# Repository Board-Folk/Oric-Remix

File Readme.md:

# Oric Remix

An updated Oric-1 / Oric Atmos board

This repository contains the Bill-of-Materials (BOM), Gerbers and Kicad files for an updated Tangerine Oric motherboard found in the Oric-1 and Oric Atmos computers. The board is compatible for system ROM, in software and in form factor with the original board. Improvements include integration of service manual modifications, updated RAM and ROM layout and composite video, with the added intention to make it easier to build. It does not replace any of the core chips including the ULA which is still required.

There was an issue with v1.1 board causing the /ROMDIS signal not disabling the internal ROM. Simon Luce discovered this in testing and devised a fix that is now incorporated into v1.2.  Many thanks to Simon. This has now been tested with the Loci expansion which now starts correctly. A suggested method of applying this fix is further down the page.

## Revisions

* Version 1.1 Initial Public Release
* Version 1.2 fix for external expansions (/ROMDIS fix)

Project now in Kicad 9

### Version 1.1 Modifications from Original

* LM7805 voltage regulator
* 27C512 ROM with 4 bank selector
* Additional AY-3-8910 socket
* Integrated tape mods (inc service manual)
* Replacement /ROMDIS logic
* AD724 composite & stereo sound output
* Speaker volume control
* 4464 RAM
* Additional system reset button
* Commodore 1531 tape interface (optional - original remains on the board)

### Version 1.2

* /ROMDIS fix

## Modification Notes

### LM7805

The original Oric boards regulated the negative power rail using a 7905 voltage regulator, keeping the positive rail common across the board and to the power supply. This has been replaced with a 7805 regulator making the ground common instead. This makes it easier to replace the regulator with something more modern and common. It has to be noted though this may cause issues sharing a power adapter with other expansions that also regulate on the negative rail, depending on how they connect to the system through the interface port. If this is the case separate power adapters should be used. We'll be testing this in time, and we're pretty sure this will have caused terrible problems for the original board too as the original regulator doesn't make a whole lot of sense for driving logic.

### ROM replacement and /ROMDIS updated

For the use of EPROMs and the bank selector, /ROMDIS was updated, the logic which allows external expansions to disable the system ROM. This uses IC11 which can no longer be omitted. This logic has been fixed in v1.2.

A 27C512 EEPROM can be used in chunks of 16KB selectable with the DIP switch. To compile a ROM of this kind, simply concatenate 4 16KB ROM images together, for example in DOS, copy /b rom1.bin+rom2.bin+rom3.bin+rom4.bin bigrom.bin to give you a 64KB file and select each 16KB banks with the switches as binary.

### AY-3-8910 socket

The AY-3-8910 can be fitted instead of the AY-3-8912 sound chip. There's no difference in function and good ones can be found more cheaply.

### Integrated Tape Mods

There were two tape mods, one from the the service manual and one from an assembled original, which have been included on the board. From the service manual page 71, modification 8, R11 and C19 "Improved Cassette Loading". R101 and C101 were also found on an original assembled board. This second mod should not be fitted for boards assembled with the 1531 tape interface.

### AD724 Composite Output

The original PROM based composite generation for the RF modulator wasn't good at all. This has been replaced with an AD724 and a 3.5mm TRRS output jack which also includes Stereo audio out, in the same channel configuration as you'd have on an Amstrad CPC464/6128. Sleeve is ground you'll need an OMTP wired cable connection.

### Speaker Volume Control

The original Oric was too loud. This adjusts the volume. Within the footprint of the volume control, there's a header for connection of an external potentiometer instead.

### System Reset Button

An additional push button has been added, with alternative pin header LK6 for external connection. This is a separate CPU reset, the original pulls down /NMI.

### Commodore 1531 Tape Port

To cut a long story short, tape support isn't great on the Oric, a source tape has to be near perfect, or you need a Maxduino. There was space on the board after all the other mods, and the schematics fitted well. It doesn't need to be fitted which is why the BOM is listed separately. The original tape connection and relay are still there with the original 7 pin DIN on the back. You can fit both fine, so long as R101 and C101 aren't fitted. It's just a cool feature and nice to have, though might upset some purists.

## Keyboard

We'll try get a keyboard replica done as soon as we can, modified for the use of MX or compatible keyswitches. There's at least one other replica already available on the internet.

A prototype PS/2 interface has been completed and works which isn't any use with an original case, but at least makes a functional system. The board also has provision for USB, the code for which hasn't been completed yet. This prototype will be uploaded soon. Still trying to work out how this will work out for a final version and whether that can fit inside a case.

## BOM

### Main BOM

Main BOM including items for Commodore 1531 Cassette. See below. Resistors 1/4W. Ceramic caps 5.08mm. Electrolytics and Tants all radial.

|Qty|Reference(s)|Value|Type|Notes|
|:--:|:--:|:--:|:--:|:--:|
|1|R1|10R|Resistor||
|1|R2|4K7|Resistor||
|10|R4,R7,R9-R11,R13,R40-R42,R56|1K|Resistor||
|1|R101|1K|Resistor|Do not fit for C1531|
|6|R5,R43-R45,R47,R49|10K|Resistor||
|1|R6|220K|Resistor||
|1|R8|100K|Resistor||
|3|R12,R46,R48|22K|Resistor||
|2|R24,R25|47K|Resistor||
|1|R26|2K2|Resistor||
|1|R30|220R|Resistor||
|3|R37-R39|270R|Resistor||
|1|R31|560R|Resistor||
|4|R32,R34-R36|75R|Resistor||
|1|C8|100uF 16V|Electrolytic||
|1|C4|2.2uF 16V|Electrolytic||
|1|C21|10uF 16V|Electrolytic||
|1|C1|22uF 16V|Electrolytic||
|1|C24|220uF 16V|Electrolytic||
|2|C3,C36|100uF Tant|Tantalum||
|1|C33|10pF|Ceramic||
|1|C26|120pF|Ceramic||
|1|C19|2.2nF|Ceramic||
|1|C101|2.2nF|Ceramic|Do not fit for C1531|
|1|C5|10nF|Ceramic||
|1|C9|220nF|Ceramic||
|5|C25,C28,C30-C32|100nF|Ceramic||
|14|C2,C7,C10-C17,C22-C23,C34,C35|47nF|Ceramic||
|1|VC1|5-20pF Trimmer|Trimmer|CVN6500|
|1|D1|1N4148|Small Signal Diode||
|1|D32|3mm LED|LED||
|1|IC1|LM7805|Voltage Regulator||
|1|IC2|LM386|IC||
|1|IC3|LM358|IC||
|1|IC4|AY-3-8912|IC|IC4 or IC10|
|1|IC10|AY-3-8910|IC|Not both|
|1|IC5|6502A|IC||
|1|IC6|6522A|IC||
|1|IC7|HCS10017|IC||
|2|IC8,IC20|74LS257|IC||
|1|IC9|27C128-27C512 ROM|IC||
|1|IC11|74LS00|IC|Clock and /ROMDIS (now a requirement)|
|1|IC21|74LS04|IC||
|1|IC22|74LS365|IC||
|1|IC23|AD724JR|IC||
|1|IC30,IC31|4464 RAM|IC||
|3|TR1-TR3|BC549|Transistor||
|1|RP1|2K2 SIP8 Bussed|Resistor Network||
|1|RP2|220R SIP8 Isolated|Resistor Network||
|1|RP3|10K SIP8 Isolated|Resistor Network||
|1|RV2|5K/10K 3386 Potentiometer|Potentiometer|5K recommended|
|1|SW1|Reset Switch (NMI)|Push Switch|Original or 6mm Push Switch|
|1|SW2|2 position DIP4 Switch|DIP Switch|Optional ROM Bank Selector 0-3 128Kb/512Kb|
|1|SW3|Reset Switch (System)|Push Switch|6mm Push Switch|
|1|RL1|Oki D51A05P|Relay||
|1|LS1|Philips AD2071/Z25|Speaker||
|1|XT1|12MHz|Crystal|HC-49/U recommended|
|1|XT2|4.43MHz|Crystal|HC-49/U recommended|
|1|SK1|5 pin DIN Socket|Socket||
|1|SK2|7 pin DIN Socket|Socket|Short, board pins 2 row, needs recommendation|
|1|SK3|2.1mm DC Barrel Jack|Socket||
|1|SK4|3.5mm TRRS Jack|Socket|PJ320A for OMTP connection|
|1|PL1|2x10 right angle pin header|Header||
|1|PL2|2x17 right angle header|Header||
|1|PL3|14 pin header|Header||

### Commodore 1531 Port BOM

|Qty|Reference(s)|Value|Type|Notes|
|:--:|:--:|:--:|:--:|:--:|
|2|R50,R51|220R|Resistor||
|1|R53|1K|Resistor||
|2|R54,R55|1K5|Resistor||
|1|C37|100nF|Ceramic||
|1|D30|1N4737A|Zener Diode|7.5V|
|1|D31|3mm LED|LED|Motor LED|
|2|TR4,TR5|BC547|Transistor||
|1|TR6|BC337|Transistor||
|1|TR7|TIP29|Transistor|D880 Substitute|
|1|SK5|7 pin mini-DIN|Socket||

## Version v1.1 /ROMDIS Fix

Version 1.1 of the board can be reasonably easily modified to incorporate the fix. Here's a suggested method.

* Cut the track to south side of IC11 pin 1 on the rear of the board
* Cut the track between pins 4 and 5 of IC11 on the rear of the board. If these pins are soldered you may wish to remove the solder first and reapply.
* Scrape to remove the solder mask on the thin track north of pin 5 on the rear of the board carefully not to expose the thicker 5V track above and re-tin.
* Solder a thin bridge wire between the exposed track and pin 5 of IC11

See image at the bottom of the page.

## Links

   [Finedon Electronics - Short 7 pin DIN socket](https://www.ebay.co.uk/itm/185588182650) <br>
   [Mike Brown's Diagnostic ROM](https://oric.signal11.org.uk/html/diagrom.htm)

## Credits

Original replica PCB Layout by Rob Taylor (@peepouk) with modifications by Ian Cudlip (@grandoldian). Original PCB, research, assistance and documentation from Chrissy (@chris_jh). Schematics recreated and modifications by Ian Cudlip with suggestions and testing from Chrissy. /ROMDIS fix by Simon Luce.

## Thanks

* "More Fun Making It" Lee (@morefunmakingit) 
* Marko Šolajić (@msolajic)
* Simon Luce
* The Board Folk Team

## Gallery

Oric Remix v1.1 in Black<br>

<br>
Version v1.1 /ROMDIS Fix<br>

## Legal

As the product of this project is a replica of a proprietary product, the the author makes no claim of copyright to the schematics nor PCB layouts and releases these into the public domain, solely for the purposes of study and historical preservation.

You are free to produce PCBs based on this project's designs at your own risk and without limitation, for your own use or for sale and/or repair at a reasonable price. Attribution is appreciated. The authors are not obliged to provide support of any kind. 

Under no circumstances will the authors be held responsible or liable in any way for losses, damages or costs resulting from the use of the information and/or resources of this project. 

The resources are provided "as-is" without warranty of any kind, either expressed or implied, including, but not limited to, the implied warranties of merchantability and fitness for a particular purpose.

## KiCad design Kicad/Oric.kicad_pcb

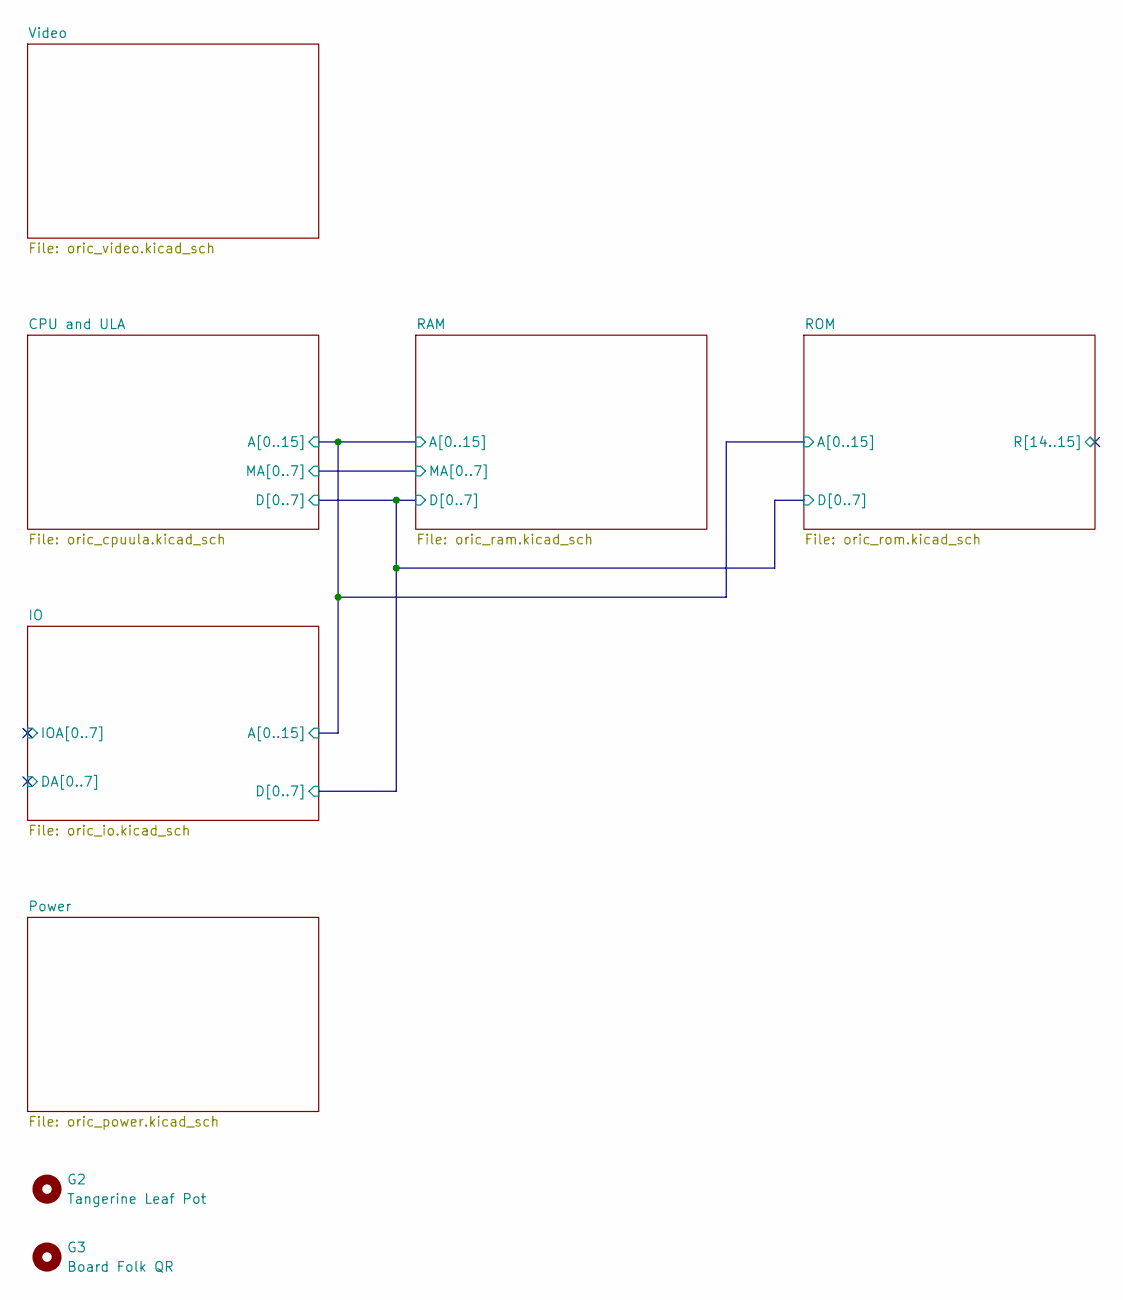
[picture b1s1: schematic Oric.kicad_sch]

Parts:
G2: Tangerine Leaf Pot; tangerineleafpot_growth1
G3: Board Folk QR; bf_qr14

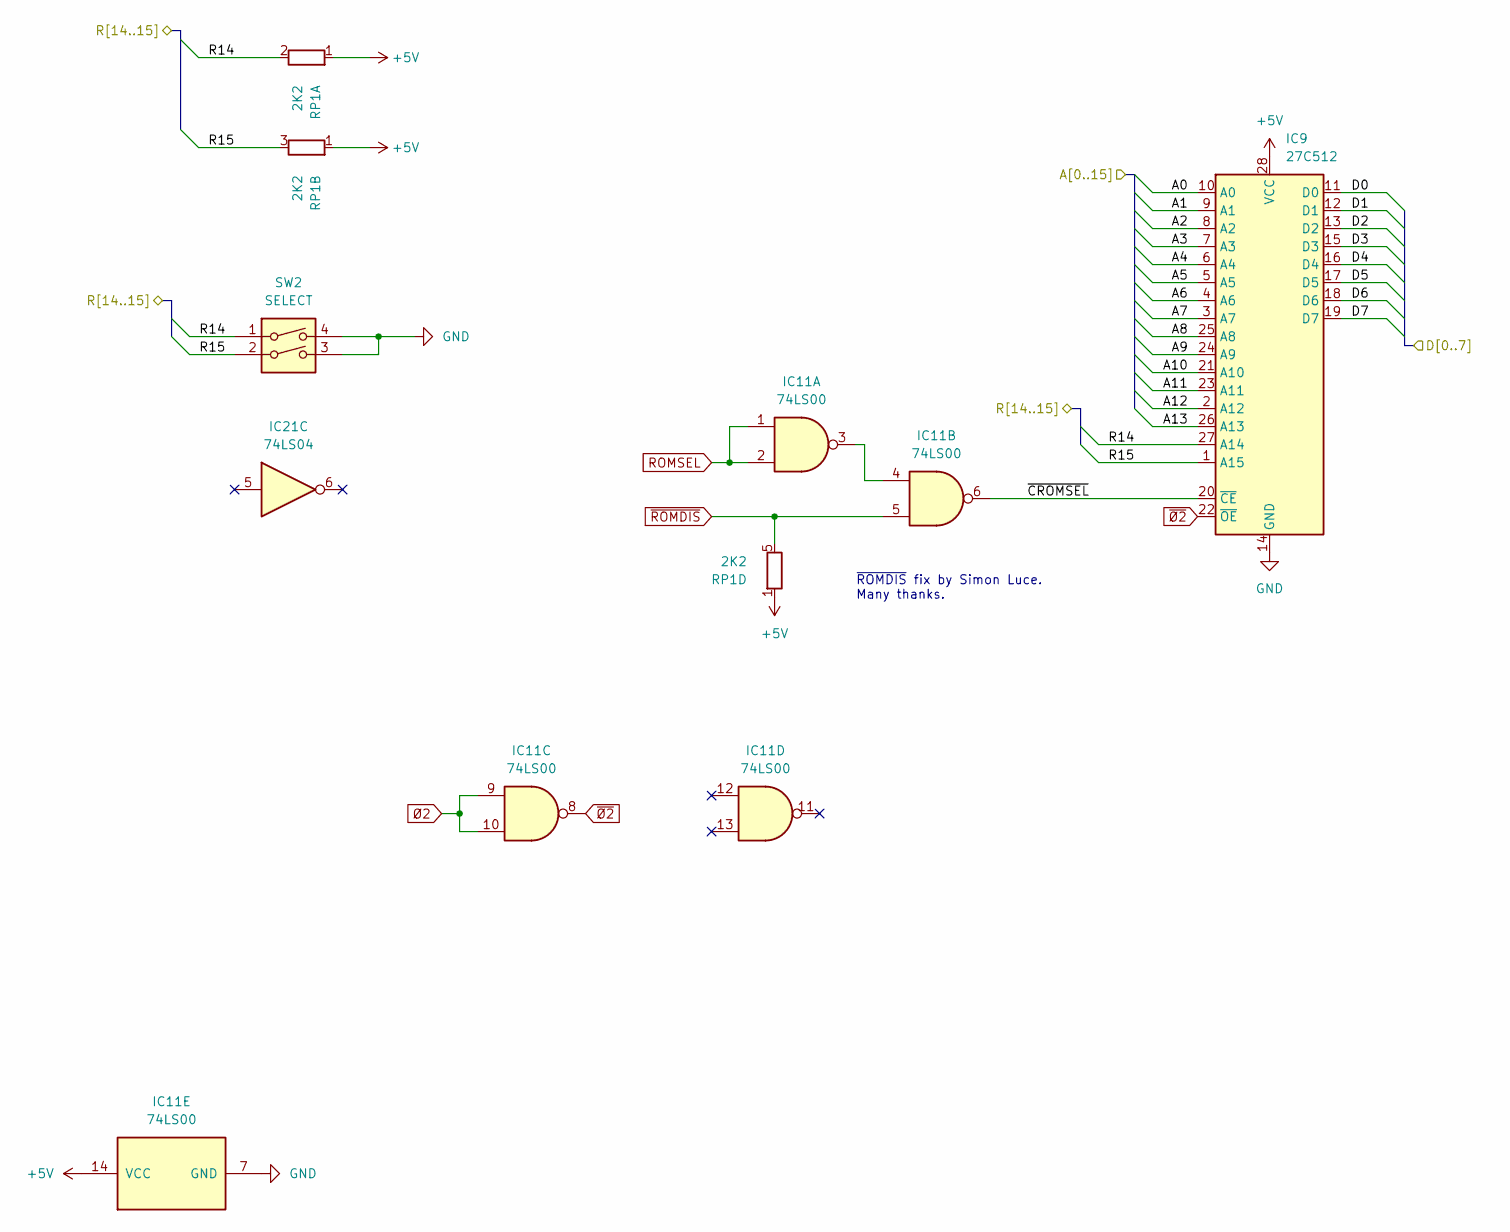
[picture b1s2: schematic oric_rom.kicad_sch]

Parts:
IC9: 27C512; DIP-28_W15.24mm
IC11: 74LS00; DIP-14_W7.62mm
IC21: 74LS04; DIP-14_W7.62mm
RP1: 2K2; R_Array_SIP8_Bussed
SW2: SELECT; ROM_Switch

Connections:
+5V: IC9.28 (VCC), IC11.14 (VCC), RP1.1 (R1); also elsewhere on the board
/CPU and ULA/A0: IC9.10 (A0); also elsewhere on the board
/CPU and ULA/A1: IC9.9 (A1); also elsewhere on the board
/CPU and ULA/A2: IC9.8 (A2); also elsewhere on the board
/CPU and ULA/A3: IC9.7 (A3); also elsewhere on the board
/CPU and ULA/A4: IC9.6 (A4); also elsewhere on the board
/CPU and ULA/A5: IC9.5 (A5); also elsewhere on the board
/CPU and ULA/A6: IC9.4 (A6); also elsewhere on the board
/CPU and ULA/A7: IC9.3 (A7); also elsewhere on the board
/CPU and ULA/A8: IC9.25 (A8); also elsewhere on the board
/CPU and ULA/A9: IC9.24 (A9); also elsewhere on the board
/CPU and ULA/A10: IC9.21 (A10); also elsewhere on the board
/CPU and ULA/A11: IC9.23 (A11); also elsewhere on the board
/CPU and ULA/A12: IC9.2 (A12); also elsewhere on the board
/CPU and ULA/A13: IC9.26 (A13); also elsewhere on the board
/CPU and ULA/D0: IC9.11 (D0); also elsewhere on the board
/CPU and ULA/D1: IC9.12 (D1); also elsewhere on the board
/CPU and ULA/D2: IC9.13 (D2); also elsewhere on the board
/CPU and ULA/D3: IC9.15 (D3); also elsewhere on the board
/CPU and ULA/D4: IC9.16 (D4); also elsewhere on the board
/CPU and ULA/D5: IC9.17 (D5); also elsewhere on the board
/CPU and ULA/D6: IC9.18 (D6); also elsewhere on the board
/CPU and ULA/D7: IC9.19 (D7); also elsewhere on the board
/ROM/R14: IC9.27 (A14), RP1.2 (R1.2), SW2.1
/ROM/R15: IC9.1 (A15), RP1.3 (R2.2), SW2.2
/ROM/~CROMSEL: IC9.20 (~CE), IC11.6
GND: IC9.14 (GND), IC11.7 (GND), SW2.3, SW2.4; also elsewhere on the board
unnamed: IC11.3, IC11.4
ROMSEL: IC11.1, IC11.2; also elsewhere on the board
~ROMDIS: IC11.5, RP1.5 (R4.2); also elsewhere on the board
~Ø2: IC9.22 (~OE), IC11.8
Ø2: IC11.9, IC11.10; also elsewhere on the board

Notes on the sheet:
~{ROMDIS} fix by Simon Luce. Many thanks.

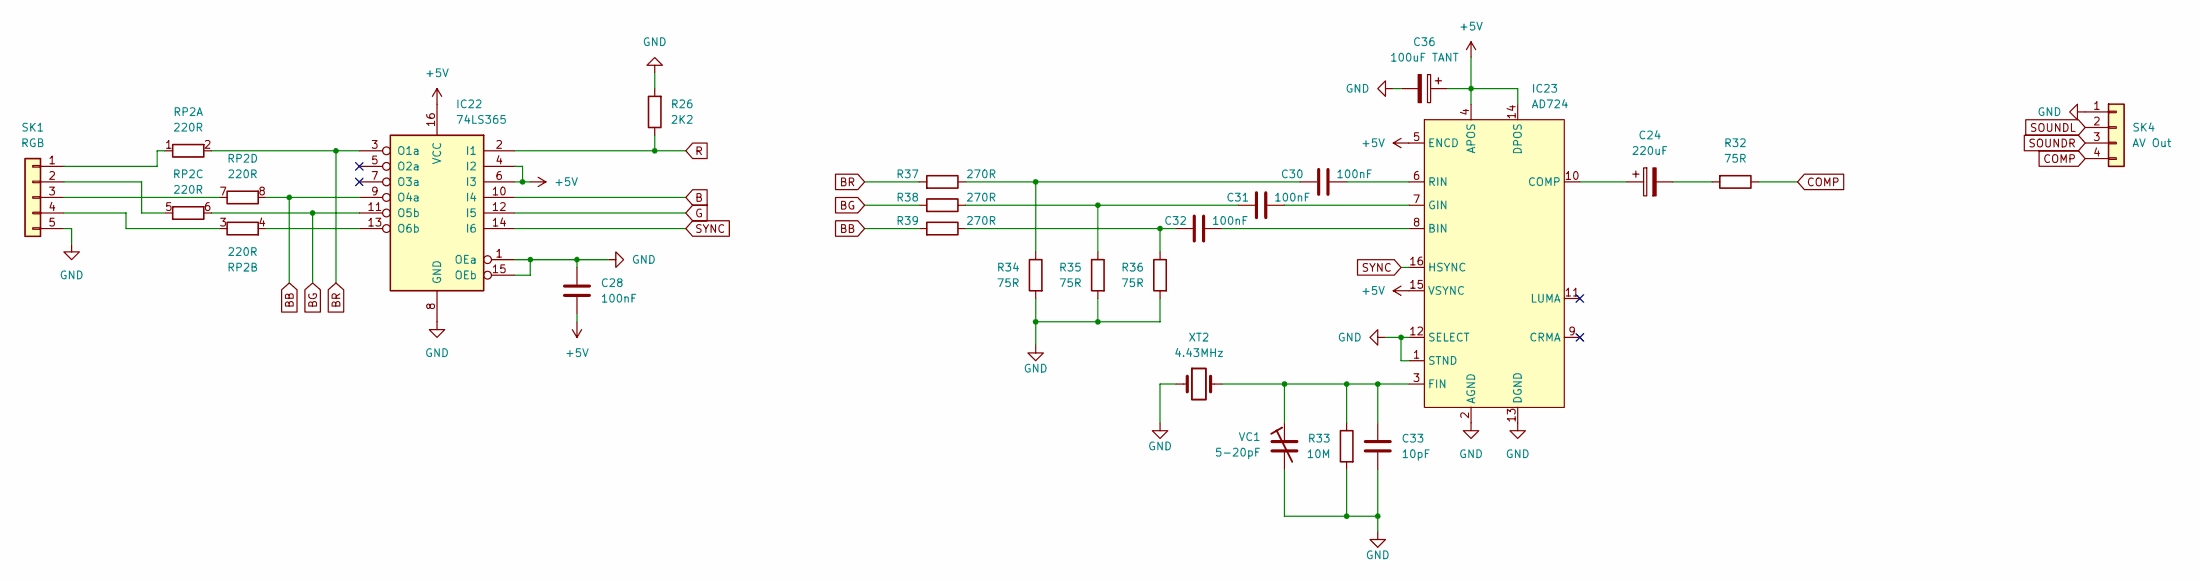
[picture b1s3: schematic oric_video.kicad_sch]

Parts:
C24: 220uF; Electrolytic Capacitor 5.00mm
C28, C30, C31, C32: 100nF; Ceramic Capacitor 5.00mm
C33: 10pF; Ceramic Capacitor 5.00mm
C36: 100uF TANT; Tantalum Capacitor 5.00mm
IC22: 74LS365; DIP-16_W7.62mm
IC23: AD724; SOIC-16W_7.5x10.3mm_P1.27mm
R26: 2K2; Resistor 10.16mm
R32, R34, R35, R36: 75R; Resistor 10.16mm
R33: 10M; Resistor 10.16mm
R37, R38, R39: 270R; Resistor 10.16mm
RP2: 220R; R_Array_SIP8_Isolated
SK1: RGB; SK1_5-Pin_DIN
SK4: AV Out; PJ320A
VC1: 5-20pF; CVN6500
XT2: 4.43MHz; Crystal

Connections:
+5V: C28.2, C36.1, IC22.4 (I2), IC22.6 (I3), IC22.16 (VCC), IC23.4 (APOS), IC23.5 (ENCD), IC23.14 (DPOS), IC23.15 (VSYNC); also elsewhere on the board
B: IC22.10 (I4); also elsewhere on the board
BB: IC22.9 (O4a), R39.2, RP2.8 (R4.2)
BG: IC22.11 (O5b), R38.2, RP2.6 (R3.2)
BR: IC22.3 (O1a), R37.2, RP2.2 (R1.2)
COMP: R32.1, SK4.4
G: IC22.12 (I5); also elsewhere on the board
GND: C28.1, C33.1, C36.2, IC22.1 (OEa), IC22.8 (GND), IC22.15 (OEb), IC23.1 (STND), IC23.2 (AGND), IC23.12 (SELECT), IC23.13 (DGND), R26.2, R33.2, R34.2, R35.2, R36.2, SK1.5, SK4.1, VC1.2, XT2.1; also elsewhere on the board
unnamed: C24.2, R32.2
unnamed: C30.1, R34.1, R37.1
unnamed: C31.1, R35.1, R38.1
unnamed: C32.1, R36.1, R39.1
unnamed: IC22.13 (O6b), RP2.4 (R2.2)
unnamed: C32.2, IC23.8 (BIN)
unnamed: C24.1, IC23.10 (COMP)
unnamed: C33.2, IC23.3 (FIN), R33.1, VC1.1, XT2.2
unnamed: C31.2, IC23.7 (GIN)
unnamed: C30.2, IC23.6 (RIN)
unnamed: RP2.1 (R1.1), SK1.1
unnamed: RP2.3 (R2.1), SK1.4
unnamed: RP2.5 (R3.1), SK1.2
unnamed: RP2.7 (R4.1), SK1.3
R: IC22.2 (I1), R26.1; also elsewhere on the board
SOUNDL: SK4.2; also elsewhere on the board
SOUNDR: SK4.3; also elsewhere on the board
SYNC: IC22.14 (I6), IC23.16 (HSYNC); also elsewhere on the board

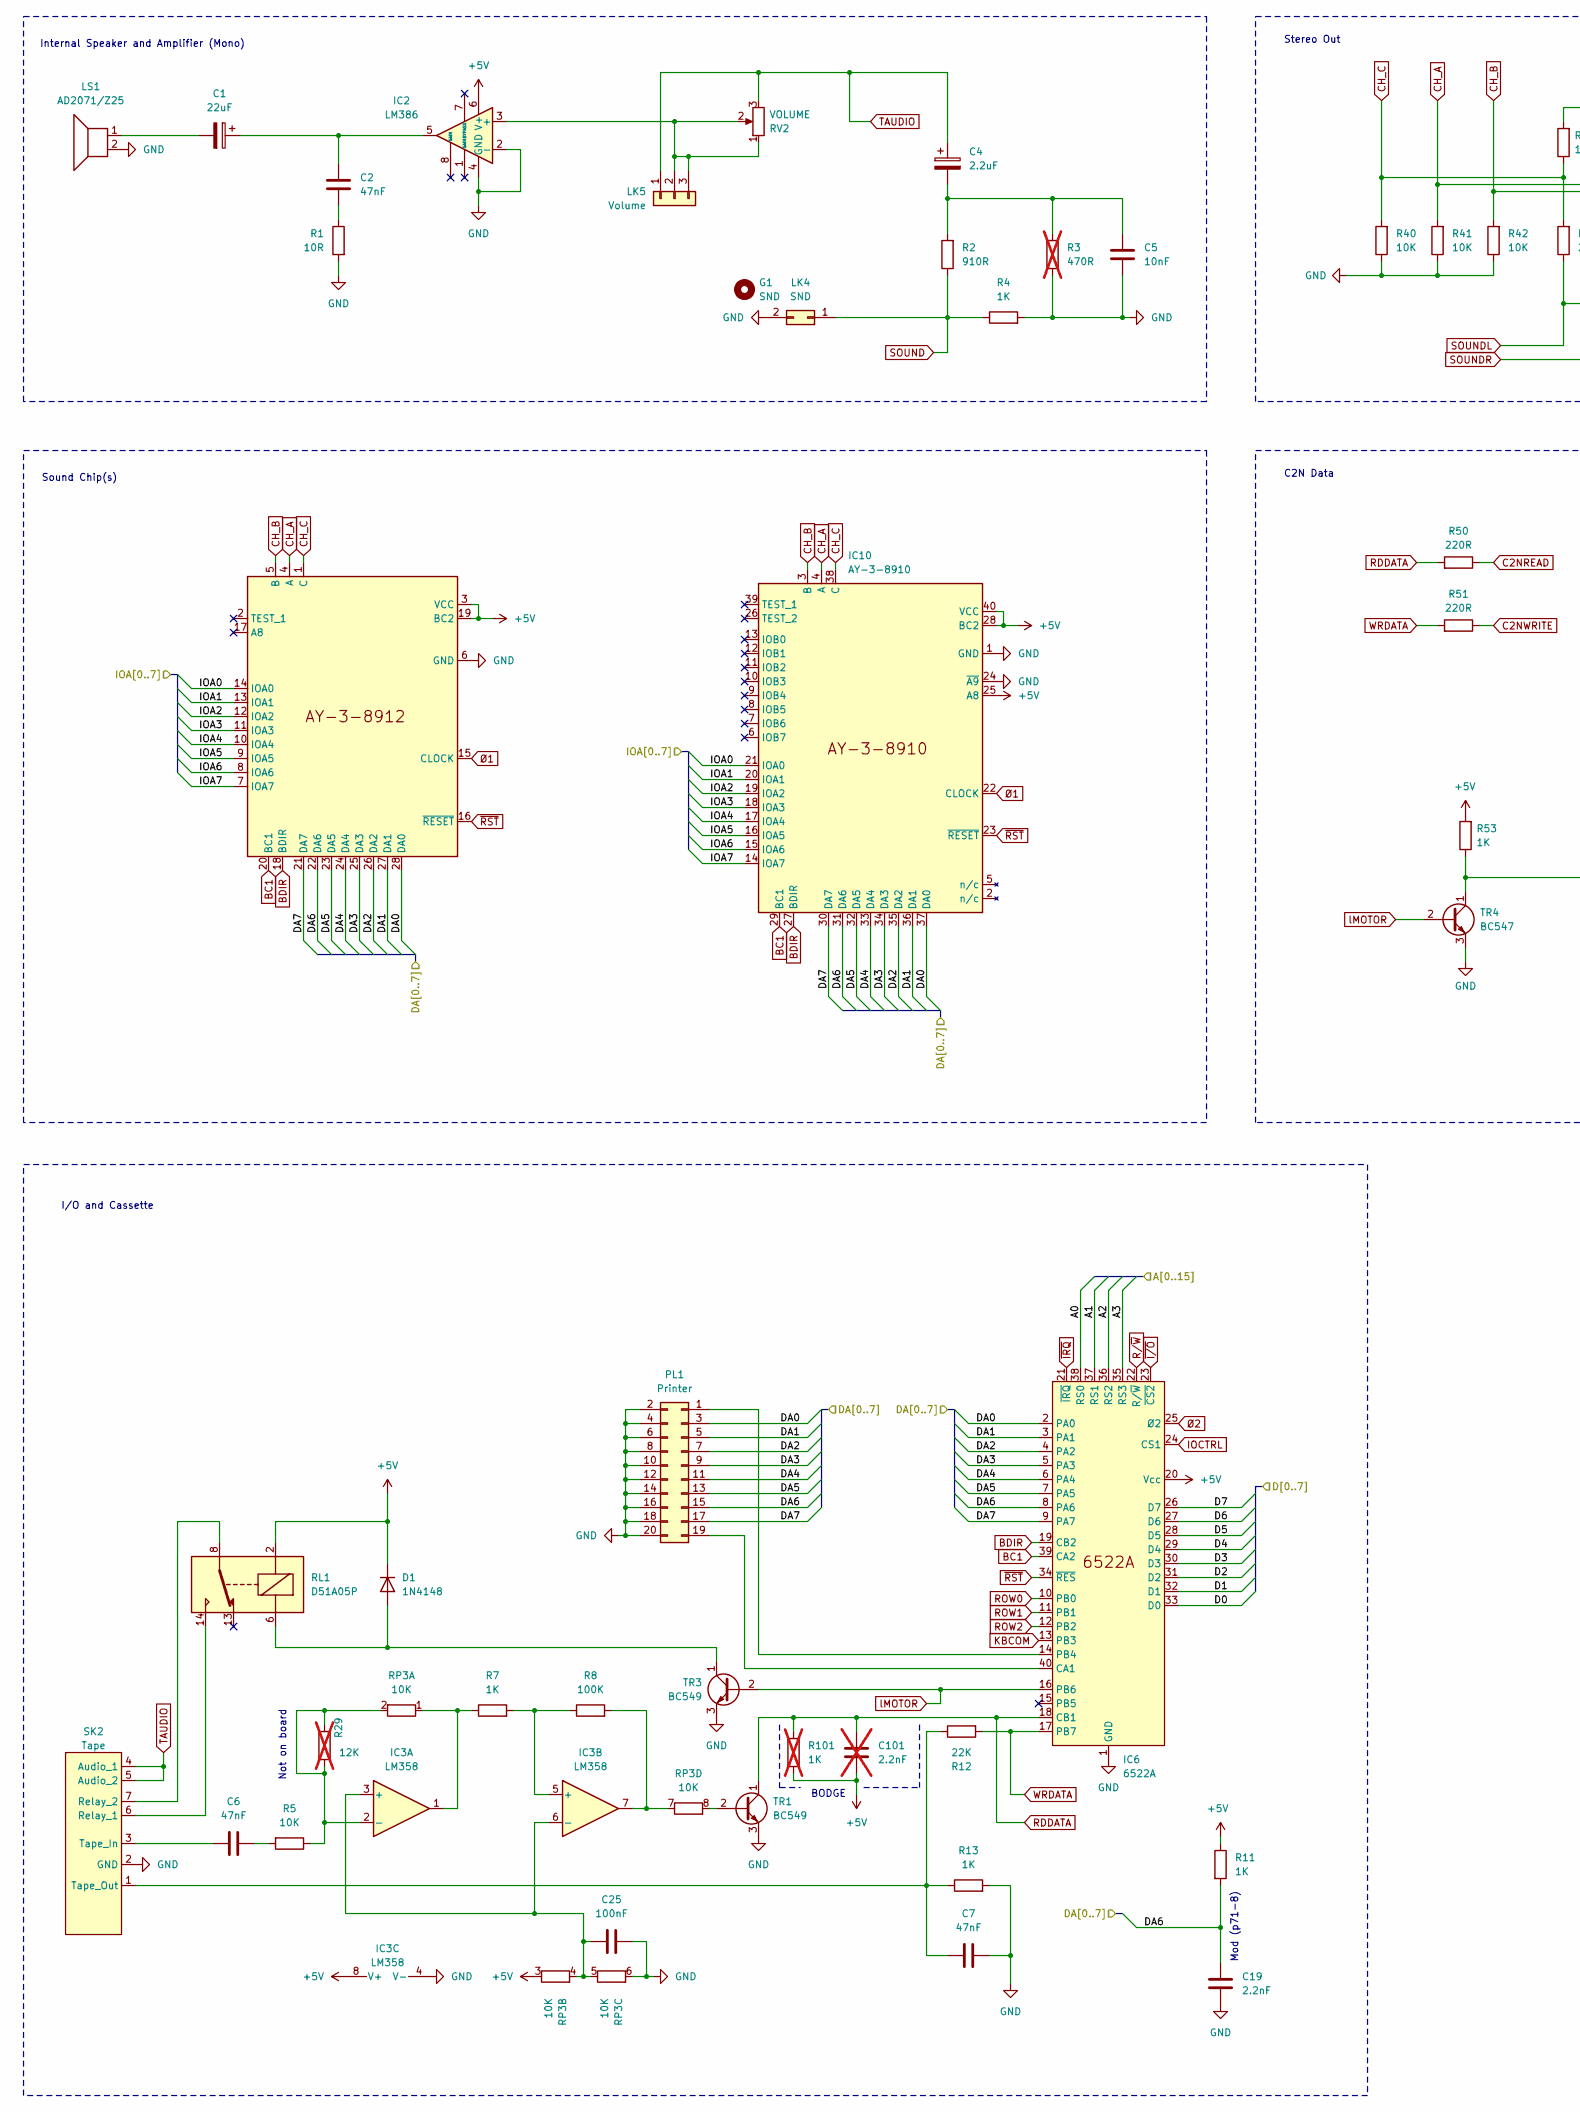
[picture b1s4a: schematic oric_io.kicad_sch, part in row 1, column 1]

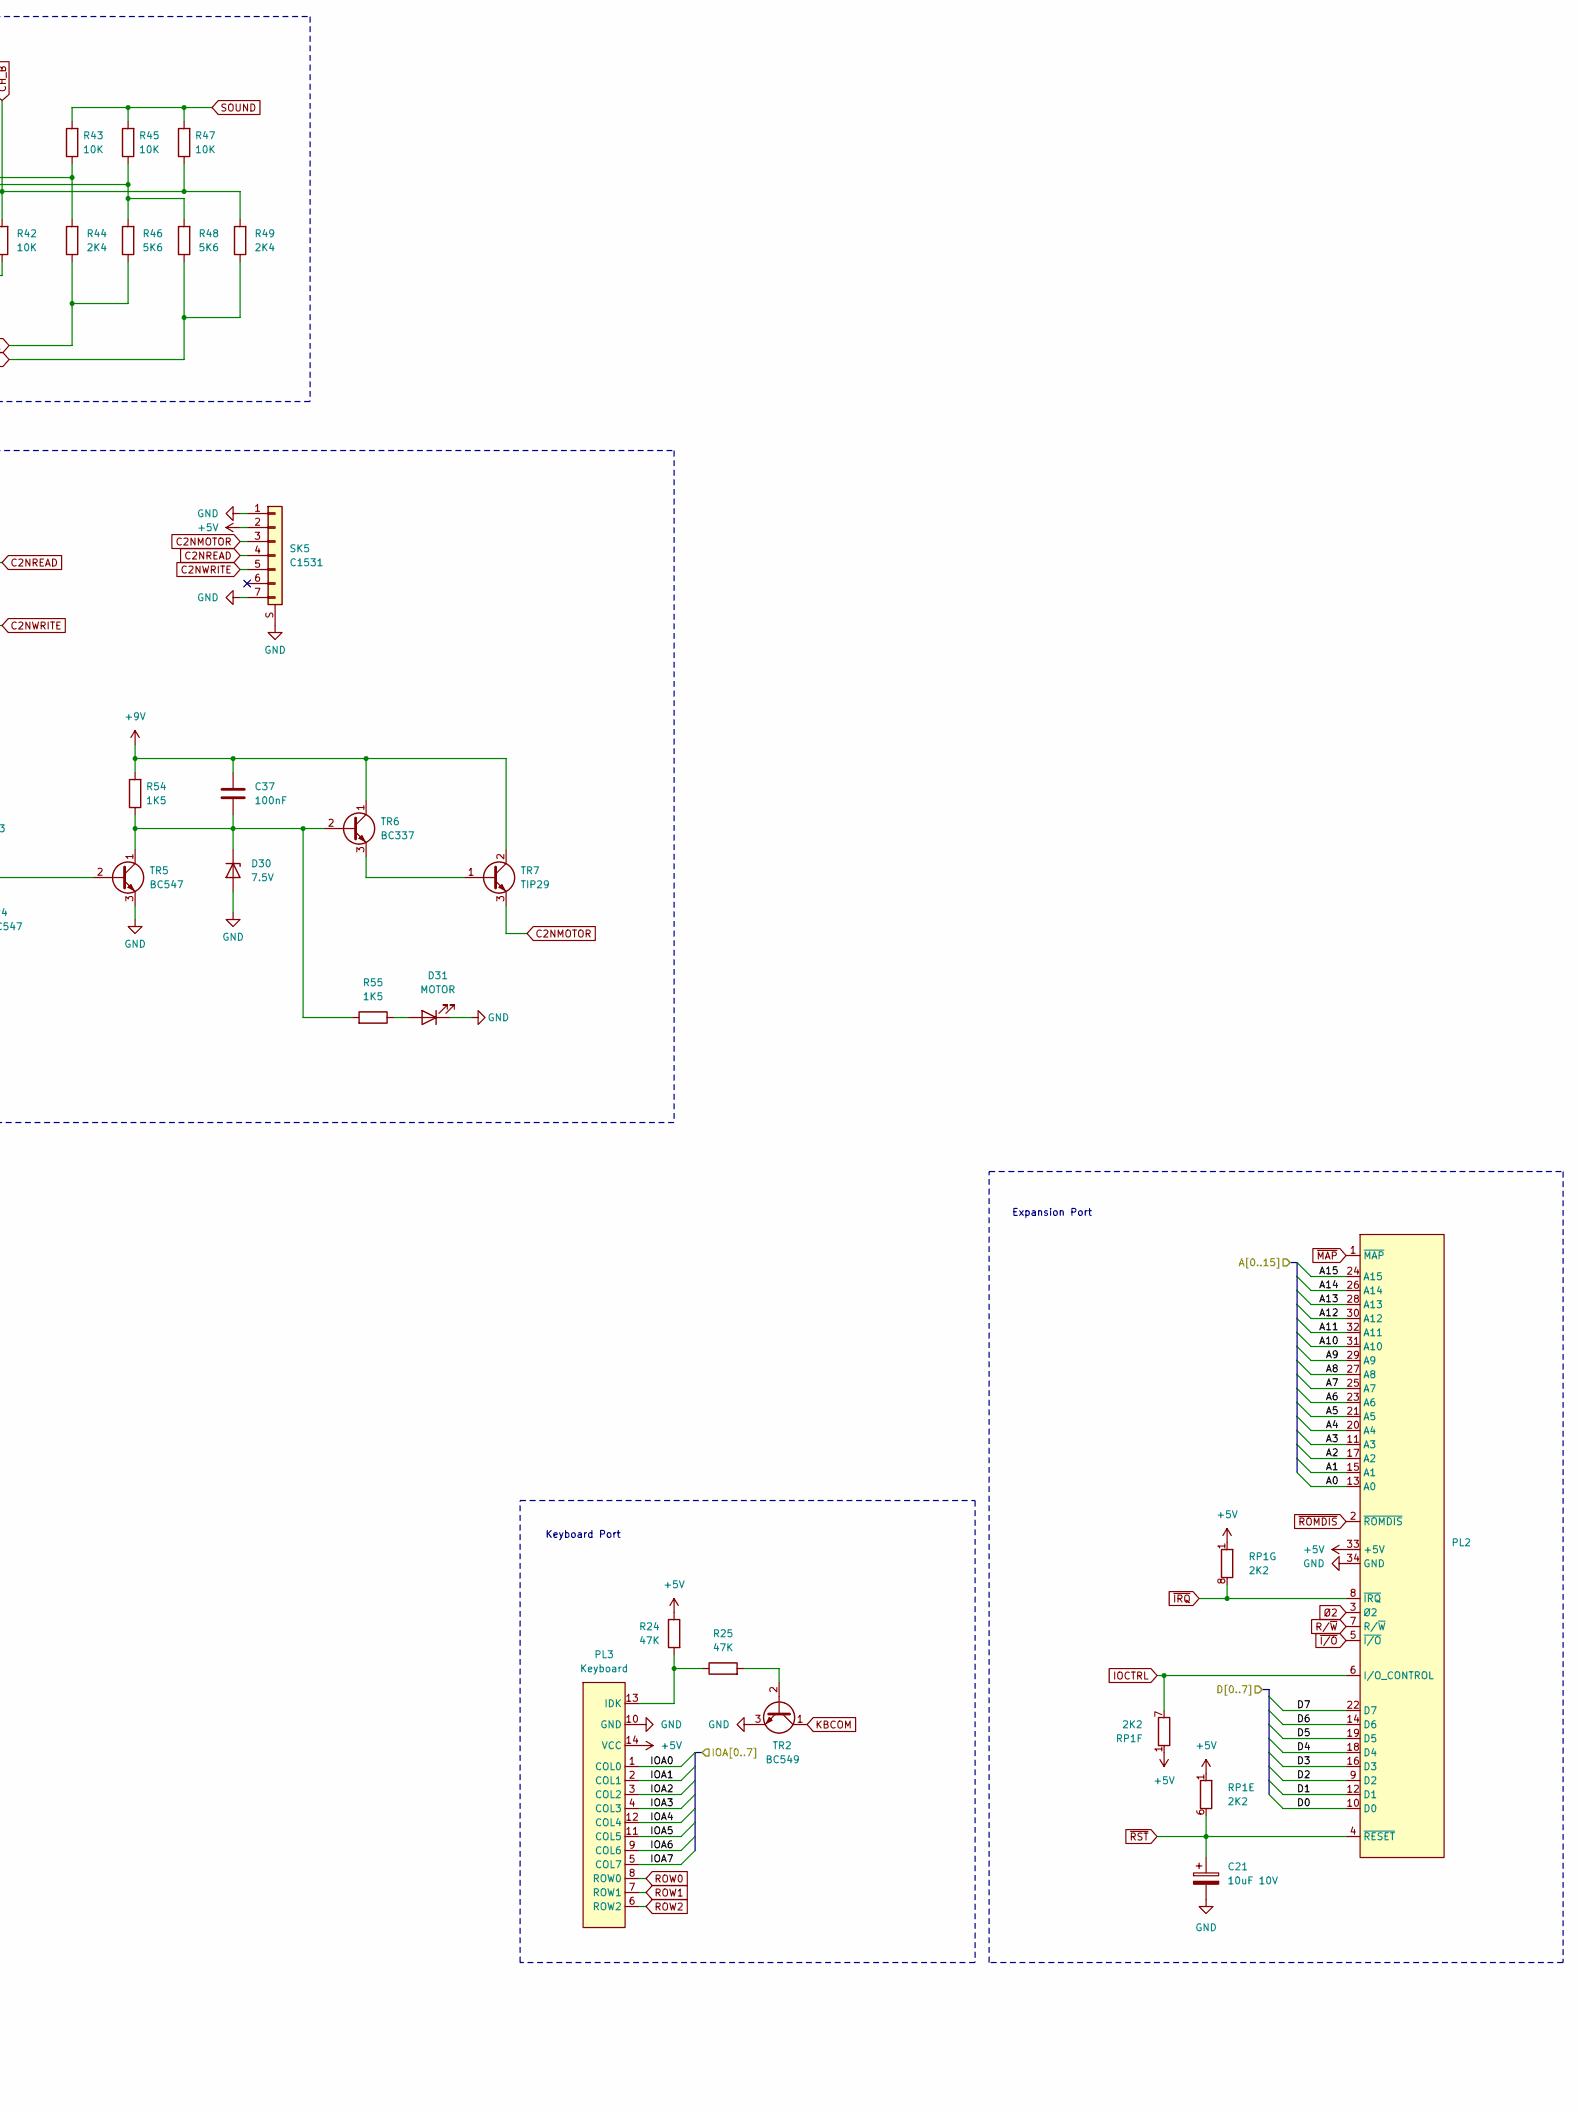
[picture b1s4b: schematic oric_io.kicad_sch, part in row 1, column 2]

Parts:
C1: 22uF; Electrolytic Capacitor 5.00mm
C2, C6, C7: 47nF; Ceramic Capacitor 5.00mm
C4: 2.2uF; Tantalum Capacitor 5.00mm
C5: 10nF; Ceramic Capacitor 5.00mm
C19: 2.2nF; Ceramic Capacitor 5.00mm
C21: 10uF 10V; Electrolytic Capacitor 5.00mm
C25, C37: 100nF; Ceramic Capacitor 5.00mm
C101: 2.2nF; Ceramic Capacitor 5.00mm; not fitted
D1: 1N4148; Diode_7.62mm
D30: 7.5V; Diode_7.62mm
D31: MOTOR; LED_D3.0mm
G1: SND; Tune
IC2: LM386; DIP-8_W7.62mm
IC3: LM358; DIP-8_W7.62mm
IC4: AY-3-8912; DIP-28_W15.24mm
IC6: 6522A; DIP-40_W15.24mm
IC10: AY-3-8910; DIP-40_W15.24mm
LK4: SND; PinHeader_1x02_P2.54mm
LK5: Volume; PinHeader_1x03_P2.54mm
LS1: AD2071/Z25; Speaker
PL1: Printer; PinHeader_2x10_P2.54mmo
PL2: PinHeader_2x17_P2.54mm
PL3: Keyboard; PinHeader_1x14_P2.54mm
R1: 10R; Resistor 10.16mm
R2: 910R; Resistor 10.16mm
R3: 470R; Resistor 10.16mm; not fitted
R4, R7, R11, R13, R53: 1K; Resistor 10.16mm
R5: 10K; Resistor 10.16mm
R8: 100K; Resistor 10.16mm
R12: 22K; Resistor 10.16mm
R24, R25: 47K; Resistor 10.16mm
R29: 12K; Resistor 10.16mm; not fitted
R40, R41, R42: 10K; Resistor 10.16mm; LCSC C482939
R43, R45, R47: 10K; Resistor 10.16mm; LCSC C84376
R44, R49: 2K4; Resistor 10.16mm; LCSC C84376
R46, R48: 5K6; Resistor 10.16mm; LCSC C114565
R50, R51: 220R; Resistor 10.16mm
R54, R55: 1K5; Resistor 10.16mm
R101: 1K; Resistor 10.16mm; not fitted
RL1: D51A05P; Relay
RP1: 2K2; R_Array_SIP8_Bussed
RP3: 10K; R_Array_SIP8_Isolated
RV2: VOLUME; Volume Control 3386
SK2: Tape; SK2 7-Pin_DIN
SK5: C1531; C1531 - 7-Pin Mini DIN
TR1, TR2, TR3: BC549; TO-92
TR4, TR5: BC547; TO-92
TR6: BC337; TO-92
TR7: TIP29; TIP29 TO-220

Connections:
+5V: C101.1, D1.1 (K), IC2.6 (V+), IC3.8 (V+), IC4.3 (VCC), IC4.19 (BC2), IC6.20 (Vcc), IC10.25 (A8), IC10.28 (BC2), IC10.40 (VCC), PL2.33 (+5V), PL3.14 (VCC), R11.1, R24.1, R53.2, R101.1, RL1.2, RP1.1 (R1), RP3.3 (R2.1), SK5.2; also elsewhere on the board
+9V: C37.1, R54.2, TR6.1 (C), TR7.2 (C); also elsewhere on the board
/CPU and ULA/A0: IC6.38 (RS0), PL2.13 (A0); also elsewhere on the board
/CPU and ULA/A1: IC6.37 (RS1), PL2.15 (A1); also elsewhere on the board
/CPU and ULA/A2: IC6.36 (RS2), PL2.17 (A2); also elsewhere on the board
/CPU and ULA/A3: IC6.35 (RS3), PL2.11 (A3); also elsewhere on the board
/CPU and ULA/A4: PL2.20 (A4); also elsewhere on the board
/CPU and ULA/A5: PL2.21 (A5); also elsewhere on the board
/CPU and ULA/A6: PL2.23 (A6); also elsewhere on the board
/CPU and ULA/A7: PL2.25 (A7); also elsewhere on the board
/CPU and ULA/A8: PL2.27 (A8); also elsewhere on the board
/CPU and ULA/A9: PL2.29 (A9); also elsewhere on the board
/CPU and ULA/A10: PL2.31 (A10); also elsewhere on the board
/CPU and ULA/A11: PL2.32 (A11); also elsewhere on the board
/CPU and ULA/A12: PL2.30 (A12); also elsewhere on the board
/CPU and ULA/A13: PL2.28 (A13); also elsewhere on the board
/CPU and ULA/A14: PL2.26 (A14); also elsewhere on the board
/CPU and ULA/A15: PL2.24 (A15); also elsewhere on the board
/CPU and ULA/D0: IC6.33 (D0), PL2.10 (D0); also elsewhere on the board
/CPU and ULA/D1: IC6.32 (D1), PL2.12 (D1); also elsewhere on the board
/CPU and ULA/D2: IC6.31 (D2), PL2.9 (D2); also elsewhere on the board
/CPU and ULA/D3: IC6.30 (D3), PL2.16 (D3); also elsewhere on the board
/CPU and ULA/D4: IC6.29 (D4), PL2.18 (D4); also elsewhere on the board
/CPU and ULA/D5: IC6.28 (D5), PL2.19 (D5); also elsewhere on the board
/CPU and ULA/D6: IC6.27 (D6), PL2.14 (D6); also elsewhere on the board
/CPU and ULA/D7: IC6.26 (D7), PL2.22 (D7); also elsewhere on the board
/IO/DA0: IC4.28 (DA0), IC6.2 (PA0), IC10.37 (DA0), PL1.3
/IO/DA1: IC4.27 (DA1), IC6.3 (PA1), IC10.36 (DA1), PL1.5
/IO/DA2: IC4.26 (DA2), IC6.4 (PA2), IC10.35 (DA2), PL1.7
/IO/DA3: IC4.25 (DA3), IC6.5 (PA3), IC10.34 (DA3), PL1.9
/IO/DA4: IC4.24 (DA4), IC6.6 (PA4), IC10.33 (DA4), PL1.11
/IO/DA5: IC4.23 (DA5), IC6.7 (PA5), IC10.32 (DA5), PL1.13
/IO/DA6: C19.1, IC4.22 (DA6), IC6.8 (PA6), IC10.31 (DA6), PL1.15, R11.2
/IO/DA7: IC4.21 (DA7), IC6.9 (PA7), IC10.30 (DA7), PL1.17
/IO/IOA0: IC4.14 (IOA0), IC10.21 (IOA0), PL3.1 (COL0)
/IO/IOA1: IC4.13 (IOA1), IC10.20 (IOA1), PL3.2 (COL1)
/IO/IOA2: IC4.12 (IOA2), IC10.19 (IOA2), PL3.3 (COL2)
/IO/IOA3: IC4.11 (IOA3), IC10.18 (IOA3), PL3.4 (COL3)
/IO/IOA4: IC4.10 (IOA4), IC10.17 (IOA4), PL3.12 (COL4)
/IO/IOA5: IC4.9 (IOA5), IC10.16 (IOA5), PL3.11 (COL5)
/IO/IOA6: IC4.8 (IOA6), IC10.15 (IOA6), PL3.9 (COL6)
/IO/IOA7: IC4.7 (IOA7), IC10.14 (IOA7), PL3.5 (COL7)
BC1: IC4.20 (BC1), IC6.39 (CA2), IC10.29 (BC1)
BDIR: IC4.18 (BDIR), IC6.19 (CB2), IC10.27 (BDIR)
C2NMOTOR: SK5.3, TR7.3 (E)
C2NREAD: R50.1, SK5.4
C2NWRITE: R51.1, SK5.5
CH_A: IC4.4 (A), IC10.4 (A), R41.2, R45.1, R46.2, R48.2
CH_B: IC4.5 (B), IC10.3 (B), R42.2, R47.1, R49.2
CH_C: IC4.1 (C), IC10.38 (C), R40.2, R43.1, R44.2
GND: C5.2, C7.2, C19.2, C21.2, C25.2, D30.2 (A), D31.1 (K), IC2.2 (-), IC2.4 (GND), IC3.4 (V-), IC4.6 (GND), IC6.1 (GND), IC10.1 (GND), IC10.24 (~A9), LK4.2, LS1.2, PL1.2, PL1.4, PL1.6, PL1.8, PL1.10, PL1.12, PL1.14, PL1.16, PL1.18, PL1.20, PL2.34 (GND), PL3.10 (GND), R1.2, R3.1, R4.2, R13.2, R40.1, R41.1, R42.1, RP3.6 (R3.2), SK2.2 (GND), SK5.1, SK5.7, SK5.S (SHIELD), TR1.3 (E), TR2.3 (E), TR3.3 (E), TR4.3 (E), TR5.3 (E); also elsewhere on the board
IOCTRL: IC6.24 (CS1), PL2.6 (I/O_CONTROL), RP1.7 (R6.2)
KBCOM: IC6.13 (PB3), TR2.1 (C)
unnamed: C1.1, C2.2, IC2.5
unnamed: C1.2, LS1.1
unnamed: C2.1, R1.1
unnamed: C4.2, C5.1, R2.2, R3.2
unnamed: C6.2, R5.2
unnamed: D1.2 (A), RL1.6, TR3.1 (C)
unnamed: C37.2, D30.1 (K), R54.1, R55.2, TR5.1 (C), TR6.2 (B)
unnamed: D31.2 (A), R55.1
unnamed: IC2.3 (+), LK5.2, LK5.3, RV2.1, RV2.2
unnamed: C25.1, IC3.3 (+), IC3.6 (-), RP3.4 (R2.2), RP3.5 (R3.1)
unnamed: IC3.2 (-), R5.1, R29.1, R29.2, RP3.2 (R1.2)
unnamed: IC3.5 (+), R7.2, R8.1
unnamed: IC6.40 (CA1), PL1.19
unnamed: IC6.14 (PB4), PL1.1
unnamed: PL3.13 (IDK), R24.2, R25.1
unnamed: IC3.1, R7.1, RP3.1 (R1.1)
unnamed: IC3.7, R8.2, RP3.7 (R4.1)
unnamed: RP3.8 (R4.2), TR1.2 (B)
unnamed: RL1.14, SK2.6 (Relay_1)
unnamed: RL1.8, SK2.7 (Relay_2)
unnamed: C6.1, SK2.3 (Tape_In)
unnamed: C7.1, R12.1, R13.1, SK2.1 (Tape_Out)
unnamed: R25.2, TR2.2 (B)
unnamed: R53.1, TR4.1 (C), TR5.2 (B)
unnamed: TR6.3 (E), TR7.1 (B)
RDDATA: C101.2, IC6.18 (CB1), R50.2, R101.2, TR1.1 (C)
ROW0: IC6.10 (PB0), PL3.8 (ROW0)
ROW1: IC6.11 (PB1), PL3.7 (ROW1)
ROW2: IC6.12 (PB2), PL3.6 (ROW2)
R/~W: IC6.22 (R/~W), PL2.7 (R/~W); also elsewhere on the board
SOUND: LK4.1, R2.1, R4.1, R43.2, R45.2, R47.2
SOUNDL: R44.1, R46.1; also elsewhere on the board
SOUNDR: R48.1, R49.1; also elsewhere on the board
TAUDIO: C4.1, LK5.1, RV2.3, SK2.4 (Audio_1), SK2.5 (Audio_2)
WRDATA: IC6.17 (PB7), R12.2, R51.2
lMOTOR: IC6.16 (PB6), TR3.2 (B), TR4.2 (B)
~IRQ: IC6.21 (~IRQ), PL2.8 (~IRQ), RP1.8 (R7.2); also elsewhere on the board
~I/O: IC6.23 (~CS2), PL2.5 (~I/O); also elsewhere on the board
~MAP: PL2.1 (~MAP); also elsewhere on the board
~ROMDIS: PL2.2 (~ROMDIS); also elsewhere on the board
~RST: C21.1, IC4.16 (~RESET), IC6.34 (~RES), IC10.23 (~RESET), PL2.4 (~RESET), RP1.6 (R5.2); also elsewhere on the board
Ø1: IC4.15 (CLOCK), IC10.22 (CLOCK); also elsewhere on the board
Ø2: IC6.25 (Ø2), PL2.3 (Ø2); also elsewhere on the board

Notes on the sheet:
I/O and Cassette
Expansion Port
Internal Speaker and Amplifier (Mono)
Sound Chip(s)
Stereo Out
Not on board
BODGE
Mod (p71-8)
Keyboard Port
C2N Data
